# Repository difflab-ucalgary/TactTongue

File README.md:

# TactTongue: Prototyping Electrotactile Stimulations on the Tongue

This is the repository that contains the hardware and software ecosystem for the "TactTongue: Prototyping Electrotactile Stimulations on the Tongue" paper (ACM UIST 2023).

# Organization
The repository is organized as follows:

Hardware: this folder contains the design schematics for the Arduino Uno and Nano boards. The designs have been simplified to ensure that there are fewer number of components and parts.

Firmware: contains the Arduino source code for generating the pulses that are sent to the electrode array.

Software: contains the source code for sending stimulation commands to the Arduino. The original TactTongue software has been written in WPF (C#.NET). The software does all the sanity checks before sending the commands to the TactTongue hardware. To ensure a wider adoption, the repository also contains the minimal Python version, allowing for sending commands through a User Interface.

# Note
Due to the concerns about unsafe AC Wall adaptors on the market, we recommend that the device be powered through a computer USB or a battery.

Code cleaning and Optimization are still in progress.

# Citation

When using or building upon this device in an academic publication, please consider citing as follows:

Dinmukhammed Mukashev, Nimesha Ranasinghe, and Aditya Shekhar Nittala. 2023. TactTongue: Prototyping ElectroTactile Stimulations on the Tongue. In The 36th Annual ACM Symposium on User Interface Software and Technology (UIST ’23), October 29-November 1, 2023, San Francisco, CA, USA. ACM, New York, NY, USA, 13 pages. https://doi.org/10.1145/3586183.3606829

# Acknowledgements
This library was adapted from work by Kurt Kaczmarek and Joel Moritz Jr.

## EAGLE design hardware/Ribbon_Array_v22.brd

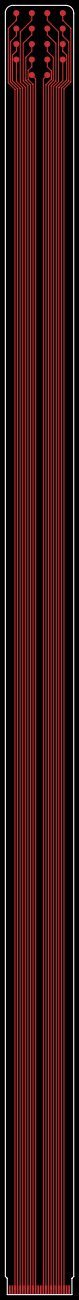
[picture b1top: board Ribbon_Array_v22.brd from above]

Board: 2 copper layers, 26.5 x 499.8 mm, 19 parts (0 on the bottom side), 18 nets.

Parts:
U$1, U$2, U$3, U$4, U$5, U$6, U$7, U$8, U$9, U$10, U$11, U$12, U$13, U$14, U$15, U$16, U$17, U$18: ELECTRODE3/32
U$19: CONECTOR; 24EDGE

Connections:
unnamed: U$1.P$1, U$19.3
unnamed: U$2.P$1, U$19.4
unnamed: U$3.P$1, U$19.5
unnamed: U$4.P$1, U$19.6
unnamed: U$5.P$1, U$19.7
unnamed: U$6.P$1, U$19.8
unnamed: U$7.P$1, U$19.9
unnamed: U$8.P$1, U$19.10
unnamed: U$9.P$1, U$19.11
unnamed: U$10.P$1, U$19.14
unnamed: U$11.P$1, U$19.15
unnamed: U$12.P$1, U$19.16
unnamed: U$13.P$1, U$19.17
unnamed: U$14.P$1, U$19.18
unnamed: U$15.P$1, U$19.19
unnamed: U$16.P$1, U$19.20
unnamed: U$17.P$1, U$19.21
unnamed: U$18.P$1, U$19.22

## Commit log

2023-07-10 test program to parse the tacttongue command
2023-07-14 parsing the command string and converting them to integer arrays
2023-07-28 Create temp
2023-08-02 Added board schematics
2023-08-02 Rename temp to readme
2023-08-02 Rename readme to README.md
2023-10-25 fixed the command issue.
2023-10-25 Updated messaging protocol
2024-05-21 .brd file for Electrode Array ribbon
2024-05-21 Fusion 360 files for Electrode Array
2024-05-21 Fusion 360 files for Arduino Nano Shield
